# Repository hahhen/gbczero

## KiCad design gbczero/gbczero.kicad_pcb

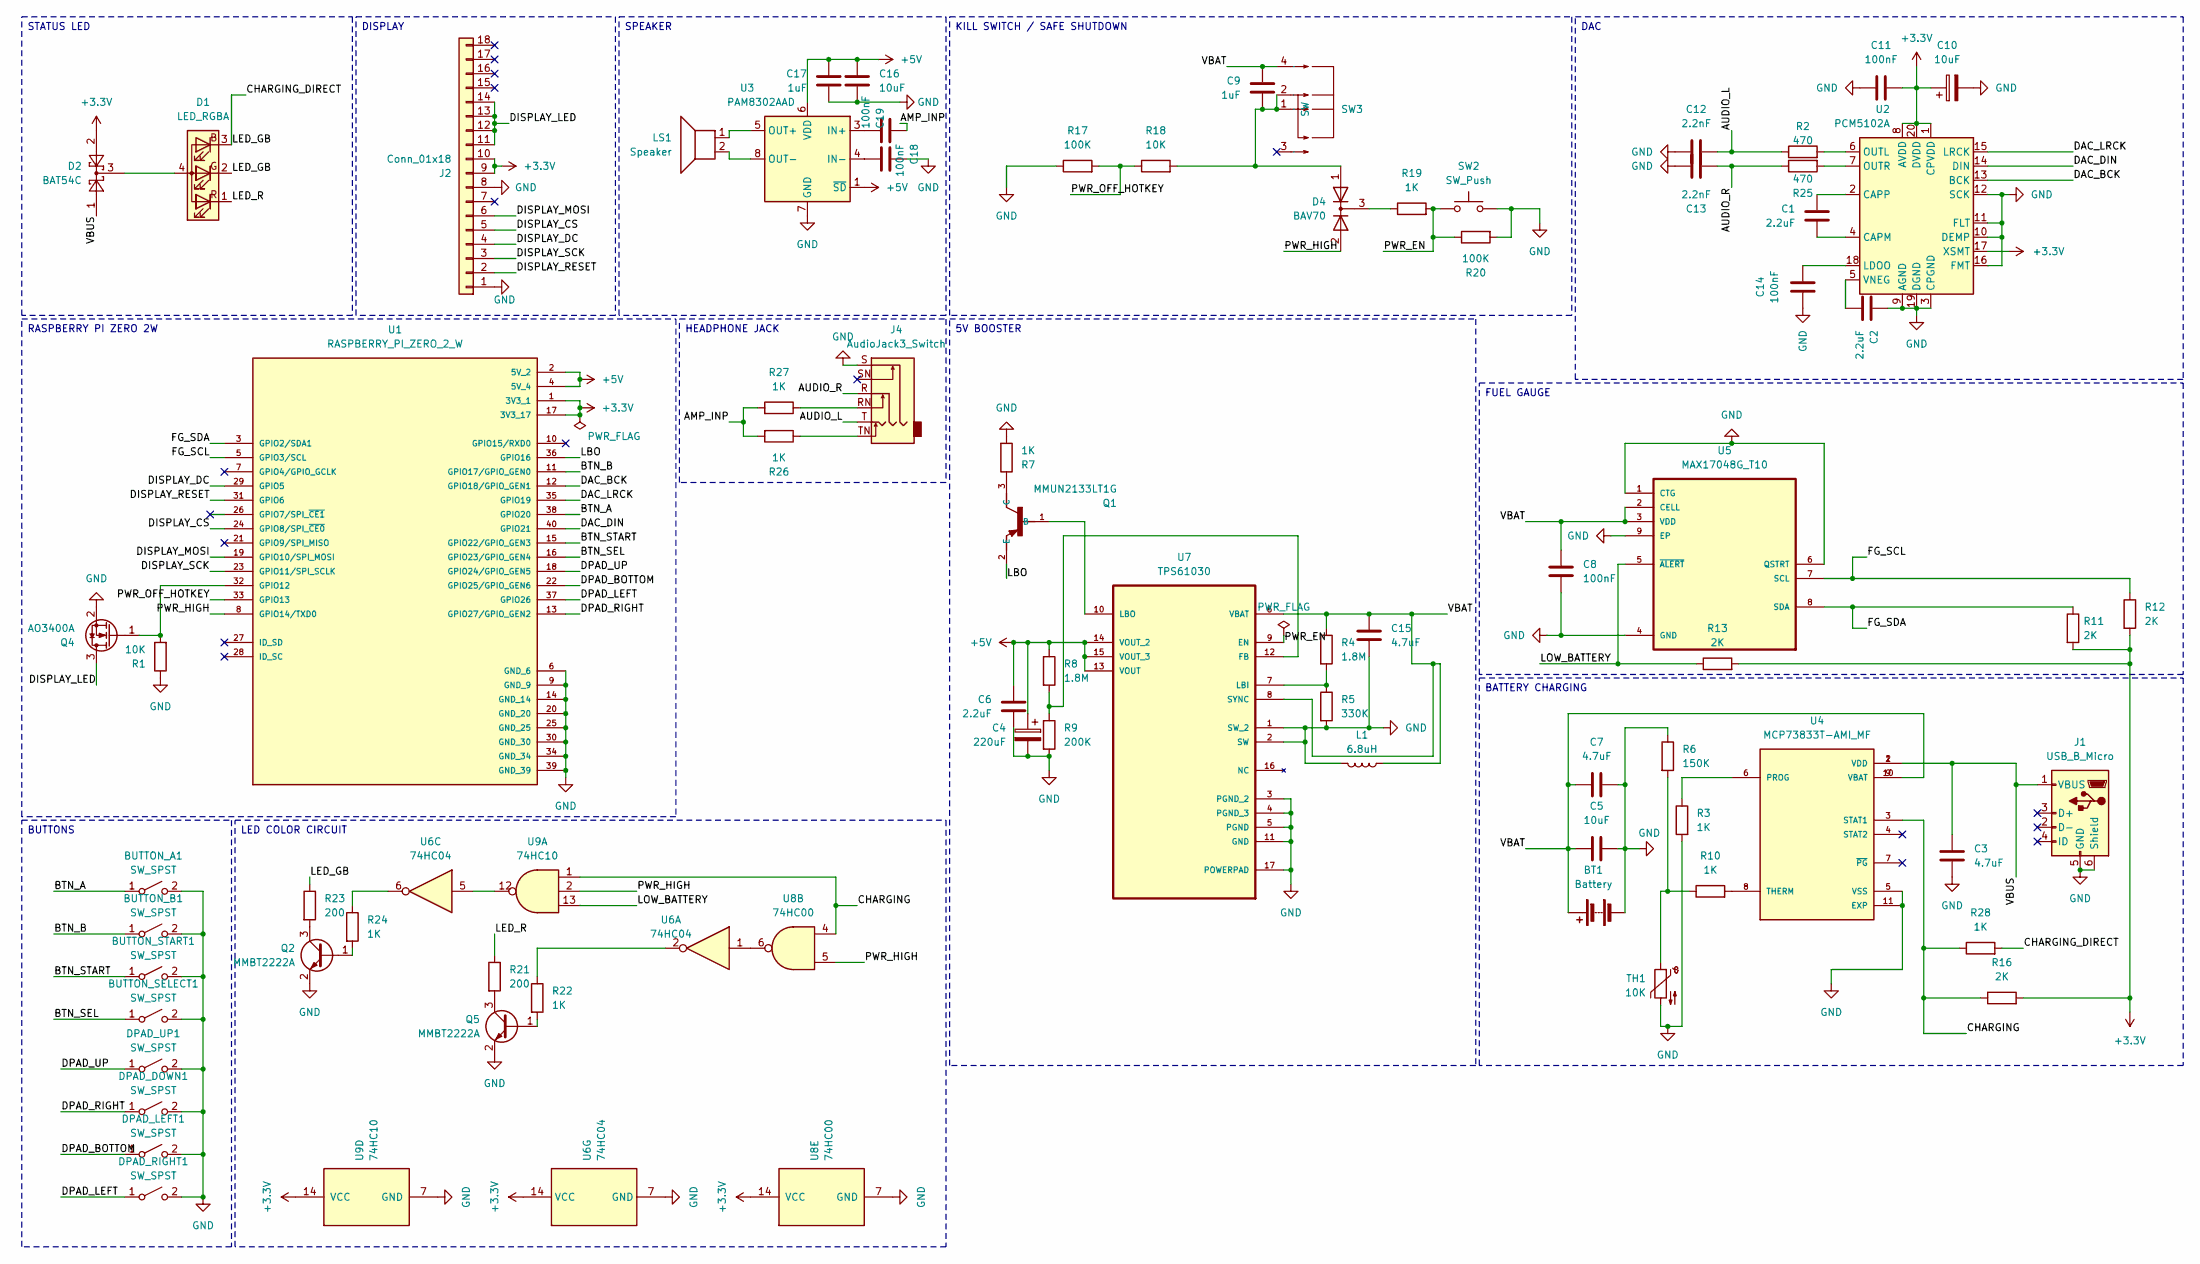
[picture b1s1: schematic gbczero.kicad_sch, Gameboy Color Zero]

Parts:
BT1: Battery; JST_PH_S2B-PH-K_1x02_P2.00mm_Horizontal
BUTTON_A1: SW_SPST; GameBoy-DMG-BTN
BUTTON_B1: SW_SPST; GameBoy-DMG-BTN
BUTTON_SELECT1: SW_SPST; GameBoy-DMG-START-SEL
BUTTON_START1: SW_SPST; GameBoy-DMG-START-SEL
C1, C2, C6: 2.2uF; C_0603_1608Metric
C3, C7, C15: 4.7uF; C_0603_1608Metric
C4: 220uF; CP_EIA-7343-31_Kemet-D
C5, C16: 10uF; C_0603_1608Metric
C8, C11, C14, C18, C19: 100nF; C_0603_1608Metric
C9, C17: 1uF; C_0603_1608Metric
C10: 10uF; CP_EIA-3216-18_Kemet-A
C12, C13: 2.2nF; C_0603_1608Metric
D1: LED_RGBA; LED_D5.0mm-4_RGB
D2: BAT54C; SOT-23
D4: BAV70; SOT-23
DPAD_DOWN1: SW_SPST; GameBoy-DMG-BTN
DPAD_LEFT1: SW_SPST; GameBoy-DMG-BTN
DPAD_RIGHT1: SW_SPST; GameBoy-DMG-BTN
DPAD_UP1: SW_SPST; GameBoy-DMG-BTN
J1: USB_B_Micro; USB_Micro-B_Molex_47346-0001
J2: Conn_01x18; Hirose_FH12-18S-0.5SH_1x18-1MP_P0.50mm_Horizontal
J4: AudioJack3_Switch; Jack_3.5mm_CUI_SJ1-3523N_Horizontal
L1: 6.8uH; L_6.3x6.3_H3
LS1: Speaker; PinHeader_1x02_P2.54mm_Vertical
Q1: MMUN2133LT1G; SOT95P240X111-3N
Q2, Q5: MMBT2222A; SOT-23
Q4: AO3400A; SOT-23
R1, R18: 10K; R_0603_1608Metric
R2, R25: 470; R_0603_1608Metric
R3, R7, R10, R19, R22, R24, R26, R27, R28: 1K; R_0603_1608Metric
R4, R8: 1.8M; R_0603_1608Metric
R5: 330K; R_0603_1608Metric
R6: 150K; R_0603_1608Metric
R9: 200K; R_0603_1608Metric
R11, R12, R13, R16: 2K; R_0603_1608Metric
R17, R20: 100K; R_0603_1608Metric
R21, R23: 200; R_0603_1608Metric
SW2: SW_Push; SW_Push_1P1T_XKB_TS-1187A
SW3: SW; SW-SMD_4P-P1.50_L3.6-W11.3; Manufacturer Part SK-1391L-2; LCSC Part Name 卧贴双档 滑动开关
TH1: 10K; R_0603_1608Metric
U1: RASPBERRY_PI_ZERO_2_W; MODULE_RASPBERRY_PI_ZERO_2_W; PARTREV April 2024
U2: PCM5102A; TSSOP-20_4.4x6.5mm_P0.65mm
U3: PAM8302AAD; SOIC-8_3.9x4.9mm_P1.27mm
U4: MCP73833T-AMI_MF; SON50P300X300X100-11N
U5: MAX17048G_T10; SON50P200X200X80-9N
U6: 74HC04; SOIC-14_3.9x8.7mm_P1.27mm
U7: TPS61030; SOP65P640X120-17N; MPN TPS61030
U8: 74HC00; SOIC-14_3.9x8.7mm_P1.27mm
U9: 74HC10; SOIC-14_3.9x8.7mm_P1.27mm

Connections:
+3.3V: C10.1, C11.1, D2.2, J2.9, J2.10, R11.2, R12.2, R13.2, R16.2, U1.1 (3V3_1), U1.17 (3V3_17), U2.1 (CPVDD), U2.8 (AVDD), U2.17 (XSMT), U2.20 (DVDD), U6.14 (VCC), U8.14 (VCC), U9.14 (VCC)
+5V: C4.1, C6.1, C16.1, C17.1, R8.1, U1.2 (5V_2), U1.4 (5V_4), U3.1 (~SD), U3.6 (VDD), U7.13 (VOUT), U7.14 (VOUT_2), U7.15 (VOUT_3)
/AMP_INP: C19.1, R26.2, R27.2
/AUDIO_L: C12.1, J4.T, R2.1
/AUDIO_R: C13.1, J4.R, R25.1
/BTN_A: BUTTON_A1.1 (A), U1.38 (GPIO20)
/BTN_B: BUTTON_B1.1 (A), U1.11 (GPIO17/GPIO_GEN0)
/BTN_SEL: BUTTON_SELECT1.1 (A), U1.16 (GPIO23/GPIO_GEN4)
/BTN_START: BUTTON_START1.1 (A), U1.15 (GPIO22/GPIO_GEN3)
/CHARGING: R16.1, R28.1, U4.3 (STAT1), U8.4, U9.1
/CHARGING_DIRECT: D1.2 (GK), D1.3 (BK), R23.1, R28.2
/DAC_BCK: U1.12 (GPIO18/GPIO_GEN1), U2.13 (BCK)
/DAC_DIN: U1.40 (GPIO21), U2.14 (DIN)
/DAC_LRCK: U1.35 (GPIO19), U2.15 (LRCK)
/DISPLAY_CS: J2.5, U1.24 (GPIO8/SPI_~CE0)
/DISPLAY_DC: J2.4, U1.29 (GPIO5)
/DISPLAY_LED: J2.11, J2.12, J2.13, J2.14, Q4.3 (D)
/DISPLAY_MOSI: J2.6, U1.19 (GPIO10/SPI_MOSI)
/DISPLAY_RESET: J2.2, U1.31 (GPIO6)
/DISPLAY_SCK: J2.3, U1.23 (GPIO11/SPI_SCLK)
/DPAD_BOTTOM: DPAD_LEFT1.1 (A), U1.22 (GPIO25/GPIO_GEN6)
/DPAD_LEFT: DPAD_RIGHT1.1 (A), U1.37 (GPIO26)
/DPAD_RIGHT: DPAD_DOWN1.1 (A), U1.13 (GPIO27/GPIO_GEN2)
/DPAD_UP: DPAD_UP1.1 (A), U1.18 (GPIO24/GPIO_GEN5)
/FG_SCL: R12.1, U1.5 (GPIO3/SCL), U5.7 (SCL)
/FG_SDA: R11.1, U1.3 (GPIO2/SDA1), U5.8 (SDA)
/LBO: Q1.2 (E), U1.36 (GPIO16)
/LED_R: D1.1 (RK), R21.1
/LOW_BATTERY: R13.1, U5.5 (~ALERT), U9.13
/PWR_EN: R19.2, R20.1, SW2.1, U7.9 (EN)
/PWR_HIGH: D4.2 (A), U1.8 (GPIO14/TXD0), U8.5, U9.2
/PWR_OFF_HOTKEY: R17.2, R18.1, U1.33 (GPIO13)
/VBAT: BT1.1 (+), C5.2, C7.2, C8.1, C9.1, C15.1, L1.1, R4.1, SW3.4, U4.9 (VBAT), U4.10 (VBAT), U5.2 (CELL), U5.3 (VDD), U7.6 (VBAT), U7.8 (SYNC)
/VBUS: C3.1, D2.1, J1.1 (VBUS), U4.1 (VDD), U4.2 (VDD)
GND: BT1.2 (-), BUTTON_A1.2 (B), BUTTON_B1.2 (B), BUTTON_SELECT1.2 (B), BUTTON_START1.2 (B), C2.1, C3.2, C4.2, C5.1, C6.2, C7.1, C8.2, C10.2, C11.2, C12.2, C13.2, C14.2, C15.2, C16.2, C17.2, C18.1, DPAD_DOWN1.2 (B), DPAD_LEFT1.2 (B), DPAD_RIGHT1.2 (B), DPAD_UP1.2 (B), J1.5 (GND), J1.6 (Shield), J2.1, J2.8, J4.S, L1.2, Q2.2 (E), Q4.2 (S), Q5.2 (E), R1.1, R3.2, R5.2, R6.1, R7.2, R9.2, R17.1, R20.2, SW2.2, TH1.2, U1.6 (GND_6), U1.9 (GND_9), U1.14 (GND_14), U1.20 (GND_20), U1.25 (GND_25), U1.30 (GND_30), U1.34 (GND_34), U1.39 (GND_39), U2.3 (CPGND), U2.9 (AGND), U2.10 (DEMP), U2.11 (FLT), U2.12 (SCK), U2.16 (FMT), U2.19 (DGND), U3.7 (GND), U4.5 (VSS), U4.11 (EXP), U5.1 (CTG), U5.4 (GND), U5.6 (QSTRT), U5.9 (EP), U6.7 (GND), U7.1 (SW_2), U7.2 (SW), U7.3 (PGND_2), U7.4 (PGND_3), U7.5 (PGND), U7.11 (GND), U7.17 (POWERPAD), U8.7 (GND), U9.7 (GND)
unnamed: C9.2, D4.1 (A), R18.2, SW3.1, SW3.2
unnamed: D1.4 (A), D2.3
unnamed: D4.3 (K), R19.1
unnamed: J4.RN, R27.1
unnamed: J4.TN, R26.1
unnamed: Q1.1 (B), U7.10 (LBO)
unnamed: Q1.3 (C), R7.1
unnamed: Q2.1 (B), R24.2
unnamed: Q2.3 (C), R23.2
unnamed: Q4.1 (G), R1.2, U1.32 (GPIO12)
unnamed: Q5.1 (B), R22.2
unnamed: Q5.3 (C), R21.2
unnamed: R6.2, R10.1, TH1.1
unnamed: R22.1, U6.2
unnamed: R24.1, U6.6
unnamed: C1.2, U2.4 (CAPM)
unnamed: C1.1, U2.2 (CAPP)
unnamed: C14.1, U2.18 (LDOO)
unnamed: R2.2, U2.6 (OUTL)
unnamed: R25.2, U2.7 (OUTR)
unnamed: C2.2, U2.5 (VNEG)
unnamed: C19.2, U3.3 (IN+)
unnamed: C18.2, U3.4 (IN-)
unnamed: LS1.1, U3.5 (OUT+)
unnamed: LS1.2, U3.8 (OUT-)
unnamed: R3.1, U4.6 (PROG)
unnamed: R10.2, U4.8 (THERM)
unnamed: U6.1, U8.6
unnamed: U6.5, U9.12
unnamed: R8.2, R9.1, U7.12 (FB)
unnamed: R4.2, R5.1, U7.7 (LBI)

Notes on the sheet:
BATTERY CHARGING
FUEL GAUGE
SPEAKER
BUTTONS
RASPBERRY PI ZERO 2W
DAC
5V BOOSTER
HEADPHONE JACK
STATUS LED
KILL SWITCH / SAFE SHUTDOWN
LED COLOR CIRCUIT
DISPLAY

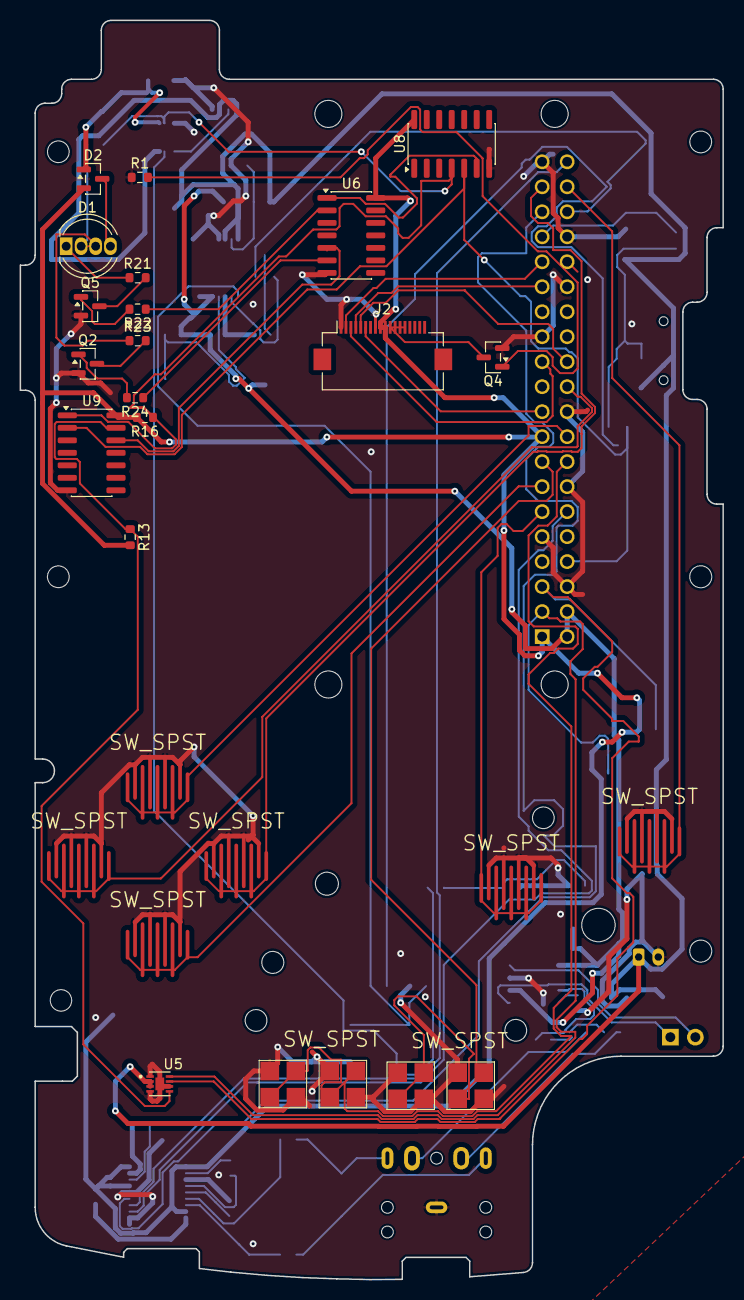
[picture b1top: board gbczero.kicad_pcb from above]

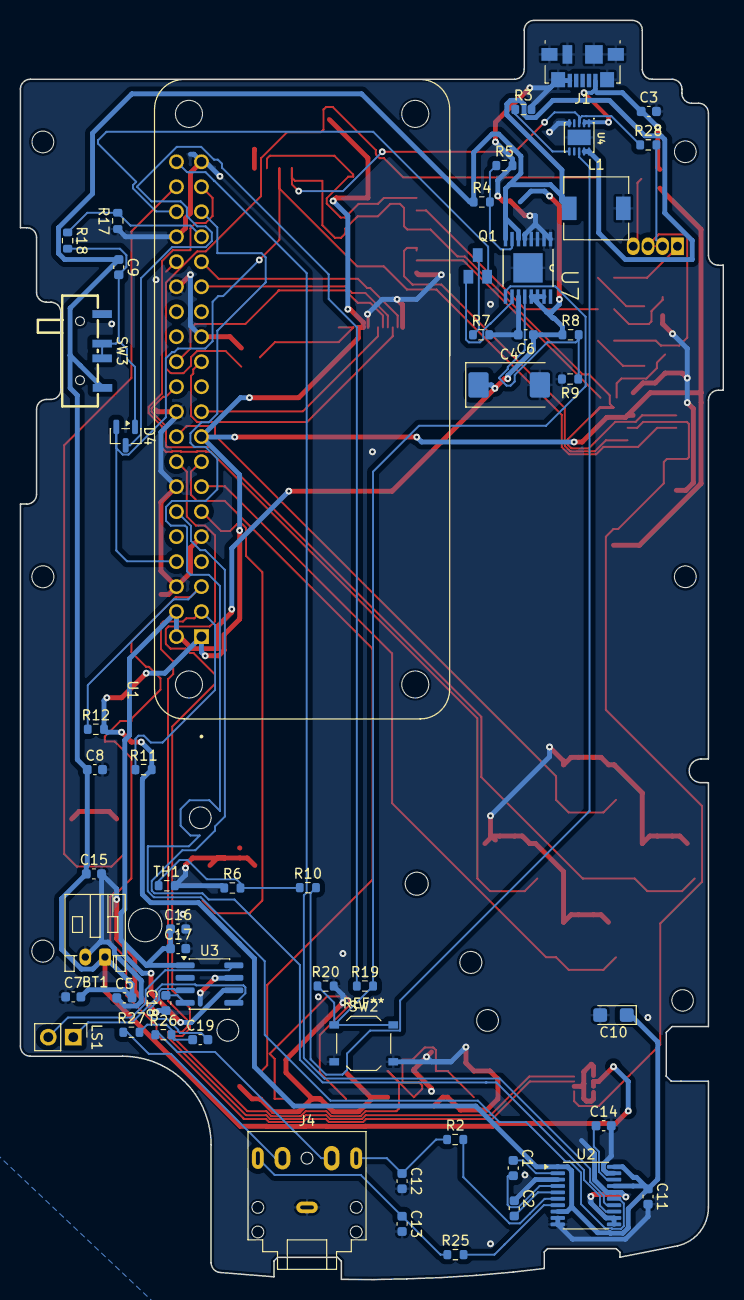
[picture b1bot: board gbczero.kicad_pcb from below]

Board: 2 copper layers, 71.4 x 128.0 mm, 78 parts (53 on the bottom side), 66 nets.

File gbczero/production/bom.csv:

Designator,Footprint,Quantity,Value,LCSC Part #
BT1,JST_PH_S2B-PH-K_1x02_P2.00mm_Horizontal,1,Battery,C265016
"BUTTON_A1, BUTTON_B1, DPAD_DOWN1, DPAD_LEFT1, DPAD_RIGHT1, DPAD_UP1",GameBoy-DMG-BTN,6,SW_SPST,
"BUTTON_SELECT1, BUTTON_START1",GameBoy-DMG-START-SEL,2,SW_SPST,
"C1, C2, C6",0603,3,2.2uF,C23630
C10,CP_EIA-3216-18_Kemet-A,1,10uF,C110055
"C11, C14, C18, C19, C8",0603,5,100nF,C14663
"C12, C13",0603,2,2.2nF,C1604
"C15, C3, C7",0603,3,4.7uF,C19666
"C16, C5",0603,2,10uF,C19702
"C17, C9",0603,2,1uF,C15849
C4,CP_EIA-7343-31_Kemet-D,1,220uF,C116577
D1,LED_D5.0mm-4_RGB,1,LED_RGBA,
D2,SOT-23,1,BAT54C,C2135
D4,SOT-23,1,BAV70,C68978
J1,USB_Micro-B_Molex_47346-0001,1,USB_B_Micro,C132560
J2,Hirose_FH12-18S-0.5SH_1x18-1MP_P0.50mm_Horizontal,1,Conn_01x18,
J4,Jack_3.5mm_CUI_SJ1-3525N_Horizontal,1,AudioJack3_Switch,C4991936
L1,L_6.3x6.3_H3,1,6.8uH,C354624
LS1,PinHeader_1x02_P2.54mm_Vertical,1,Speaker,
Q1,SOT95P240X111-3N,1,MMUN2133LT1G,C86182
"Q2, Q5",SOT-23,2,MMBT2222A,C8512
Q4,SOT-23,1,AO3400A,C20917
"R1, R18",0603,2,10K,C25804
"R10, R19, R22, R24, R26, R27, R28, R3, R7",0603,9,1K,C21190
"R11, R12, R13, R16",0603,4,2K,C22975
"R17, R20",0603,2,100K,C25803
"R2, R25",0603,2,470,C23179
"R21, R23",0603,2,200,C8218
"R4, R8",0603,2,1.8M,C13318
R5,0603,1,330K,C23137
R6,0603,1,150K,C22807
R9,0603,1,200K,C25811
SW2,SW_Push_1P1T_XKB_TS-1187A,1,SW_Push,C318884
SW3,SW-SMD_4P-P1.50_L3.6-W11.3,1,SW,C319026
U1,MODULE_RASPBERRY_PI_ZERO_2_W,1,RASPBERRY_PI_ZERO_2_W,
U2,TSSOP-20_4.4x6.5mm_P0.65mm,1,PCM5102A,C107671
U3,SOIC-8_3.9x4.9mm_P1.27mm,1,PAM8302AAD,C112137
U4,SON50P300X300X100-11N,1,MCP73833T-AMI_MF,C340160
U5,SON50P200X200X80-9N,1,MAX17048G_T10,C2682616
U6,SOIC-14_3.9x8.7mm_P1.27mm,1,74HC04,C5590
U7,SOP65P640X120-17N,1,TPS61030,C9842
U8,SOIC-14_3.9x8.7mm_P1.27mm,1,74HC00,C5586
U9,SOIC-14_3.9x8.7mm_P1.27mm,1,74HC10,C6816
TH1,0603,1,,

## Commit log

2025-11-20 First iteration
2025-12-25 almost done
2025-12-25 zero errors
2025-12-26 Finished (maybe)
2025-12-29 I'll change some things in a bit
